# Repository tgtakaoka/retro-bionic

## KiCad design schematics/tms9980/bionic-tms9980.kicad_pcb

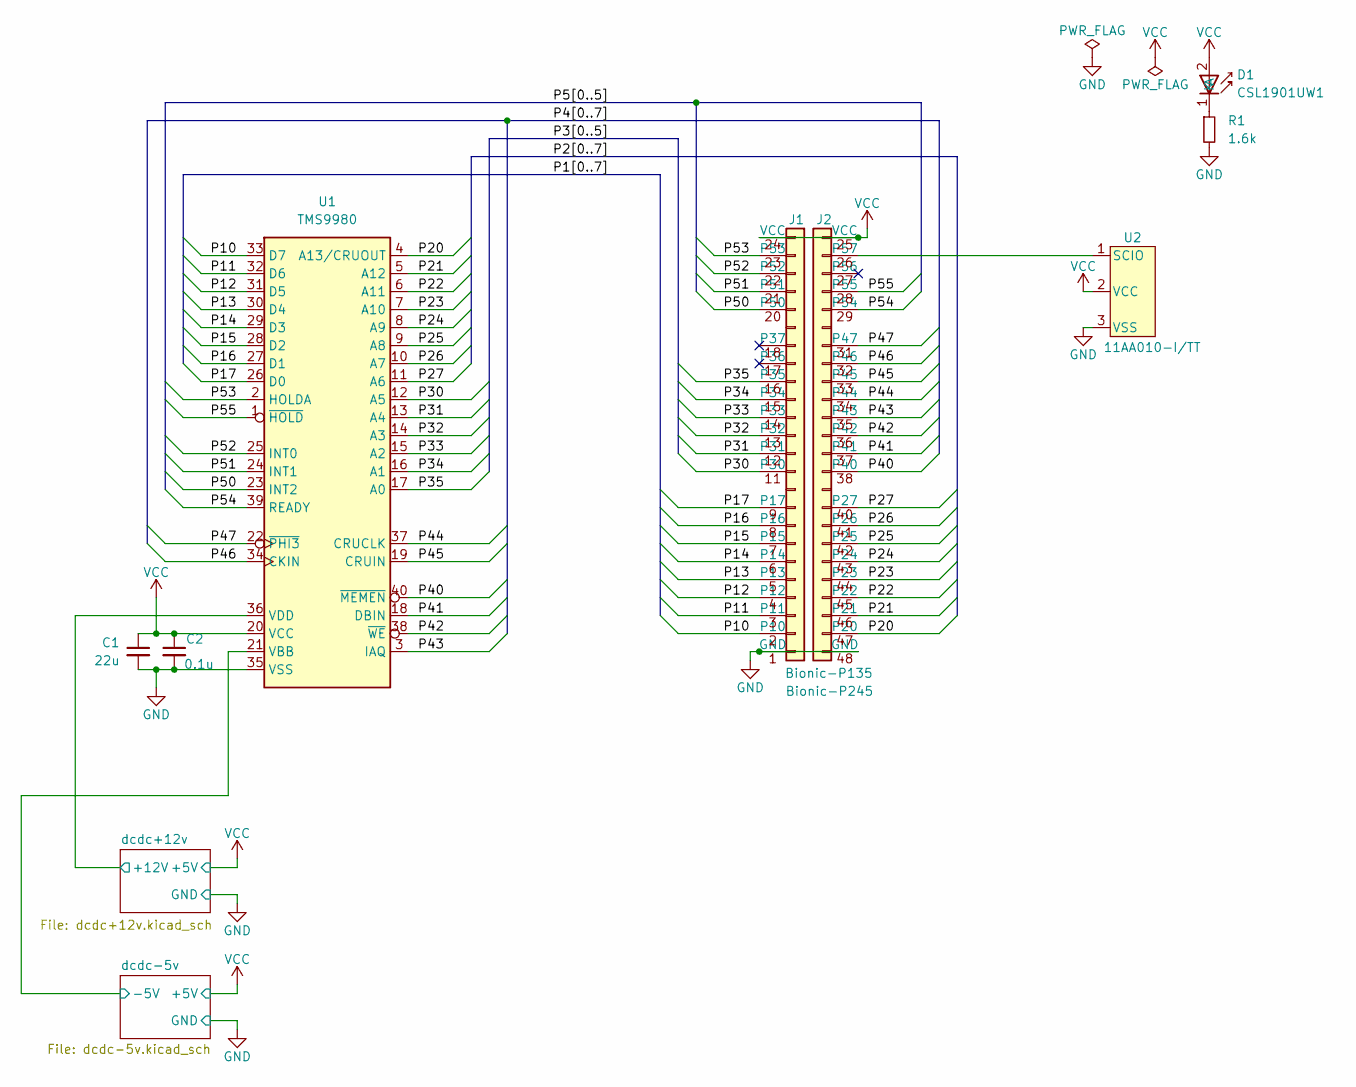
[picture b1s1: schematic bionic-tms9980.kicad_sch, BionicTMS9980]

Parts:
C1: 22u; C_0603_1608Metric_Pad1.08x0.95mm_HandSolder
C2: 0.1u; C_0603_1608Metric_Pad1.08x0.95mm_HandSolder
D1: CSL1901UW1; LED_CSL1901UW1_ROM-M
J1: Bionic-P135; Bionic-P135_THT
J2: Bionic-P245; Bionic-P245_THT
R1: 1.6k; R_0603_1608Metric_Pad0.98x0.95mm_HandSolder
U1: TMS9980; DIP-40_W15.24mm_Socket
U2: 11AA010-I/TT; SOT-23_MC_MCH-M

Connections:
/P10: J1.2 (P10), U1.33 (D7)
/P11: J1.3 (P11), U1.32 (D6)
/P12: J1.4 (P12), U1.31 (D5)
/P13: J1.5 (P13), U1.30 (D4)
/P14: J1.6 (P14), U1.29 (D3)
/P15: J1.7 (P15), U1.28 (D2)
/P16: J1.8 (P16), U1.27 (D1)
/P17: J1.9 (P17), U1.26 (D0)
/P20: J2.47 (P20), U1.4 (A13/CRUOUT)
/P21: J2.46 (P21), U1.5 (A12)
/P22: J2.45 (P22), U1.6 (A11)
/P23: J2.44 (P23), U1.7 (A10)
/P24: J2.43 (P24), U1.8 (A9)
/P25: J2.42 (P25), U1.9 (A8)
/P26: J2.41 (P26), U1.10 (A7)
/P27: J2.40 (P27), U1.11 (A6)
/P30: J1.11 (P30), U1.12 (A5)
/P31: J1.12 (P31), U1.13 (A4)
/P32: J1.13 (P32), U1.14 (A3)
/P33: J1.14 (P33), U1.15 (A2)
/P34: J1.15 (P34), U1.16 (A1)
/P35: J1.16 (P35), U1.17 (A0)
/P40: J2.38 (P40), U1.40 (~MEMEN)
/P41: J2.37 (P41), U1.18 (DBIN)
/P42: J2.36 (P42), U1.38 (~WE)
/P43: J2.35 (P43), U1.3 (IAQ)
/P44: J2.34 (P44), U1.37 (CRUCLK)
/P45: J2.33 (P45), U1.19 (CRUIN)
/P46: J2.32 (P46), U1.34 (CKIN)
/P47: J2.31 (P47), U1.22 (~PHI3)
/P50: J1.20 (P50), U1.23 (INT2)
/P51: J1.21 (P51), U1.24 (INT1)
/P52: J1.22 (P52), U1.25 (INT0)
/P53: J1.23 (P53), U1.2 (HOLDA)
/P54: J2.29 (P54), U1.39 (READY)
/P55: J2.28 (P55), U1.1 (~HOLD)
/dcdc+12v/+12V: U1.36 (VDD); also elsewhere on the board
/dcdc-5v/-5V: U1.21 (VBB); also elsewhere on the board
GND: C1.2, C2.2, J1.1 (GND), J2.48 (GND), R1.2, U1.35 (VSS), U2.3 (VSS); also elsewhere on the board
unnamed: D1.1 (K), R1.1
unnamed: J2.26 (P57), U2.1 (SCIO)
VCC: C1.1, C2.1, D1.2 (A), J1.24 (VCC), J2.25 (VCC), U1.20 (VCC), U2.2 (VCC); also elsewhere on the board

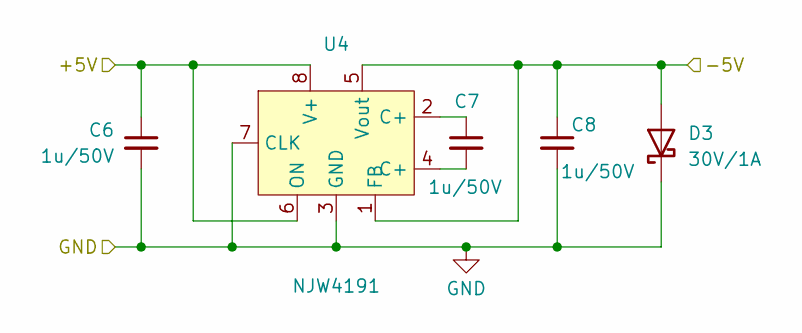
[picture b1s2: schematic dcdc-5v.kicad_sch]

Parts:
C6, C7, C8: 1u/50V; C_0603_1608Metric_Pad1.08x0.95mm_HandSolder
D3: 30V/1A; CR_60M-60_ROM-M
U4: NJW4191; MSOP8VSP8_PI-VSP8-E-B_NMD-M

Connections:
/dcdc-5v/-5V: C8.1, D3.2 (A), U4.1 (FB), U4.5 (Vout); also elsewhere on the board
GND: C6.2, C8.2, D3.1 (K), U4.3 (GND), U4.7 (CLK); also elsewhere on the board
unnamed: C7.1, U4.2 (C+)
unnamed: C7.2, U4.4 (C+)
VCC: C6.1, U4.6 (ON), U4.8 (V+); also elsewhere on the board

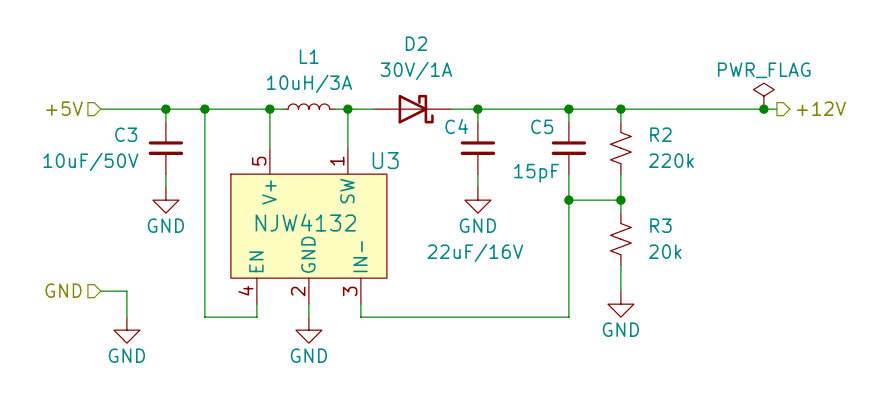
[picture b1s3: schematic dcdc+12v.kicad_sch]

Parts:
C3: 10uF/50V; C_0603_1608Metric_Pad1.08x0.95mm_HandSolder
C4: 22uF/16V; C_0603_1608Metric_Pad1.08x0.95mm_HandSolder
C5: 15pF; C_0603_1608Metric_Pad1.08x0.95mm_HandSolder
D2: 30V/1A; CR_60M-60_ROM-M
L1: 10uH/3A; IND_DFE322512F_MUR-M
R2: 220k; R_0603_1608Metric_Pad0.98x0.95mm_HandSolder
R3: 20k; R_0603_1608Metric_Pad0.98x0.95mm_HandSolder
U3: NJW4132; SOT-89-5_NMD-M

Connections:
/dcdc+12v/+12V: C4.1, C5.1, D2.1 (K), R2.1; also elsewhere on the board
GND: C3.2, C4.2, R3.2, U3.2 (GND); also elsewhere on the board
unnamed: D2.2 (A), L1.2, U3.1 (SW)
unnamed: C5.2, R2.2, R3.1, U3.3 (IN-)
VCC: C3.1, L1.1, U3.4 (EN), U3.5 (V+); also elsewhere on the board

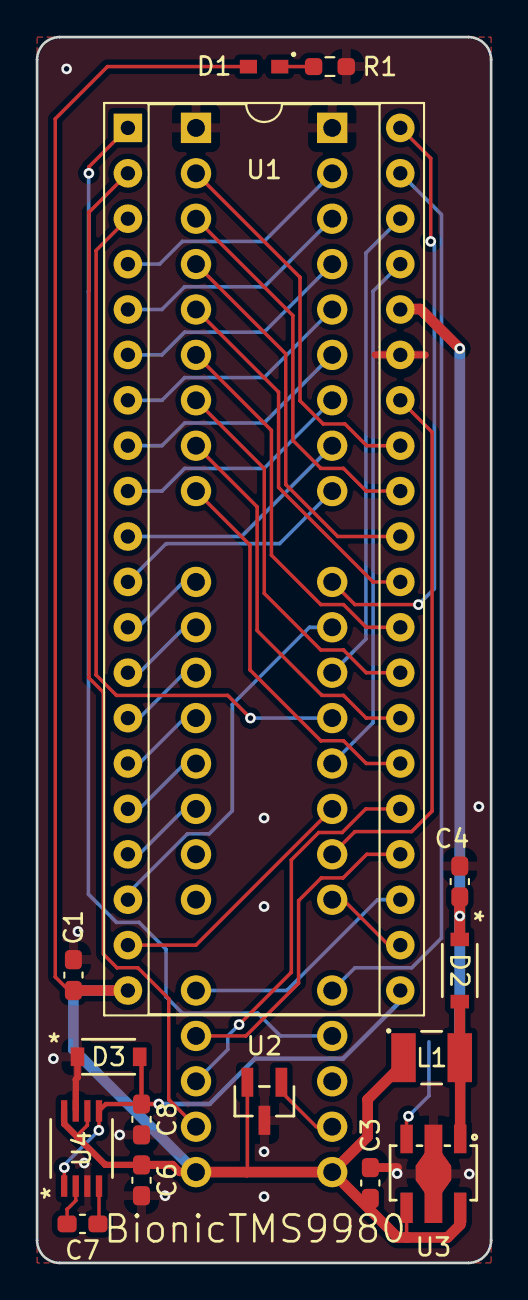
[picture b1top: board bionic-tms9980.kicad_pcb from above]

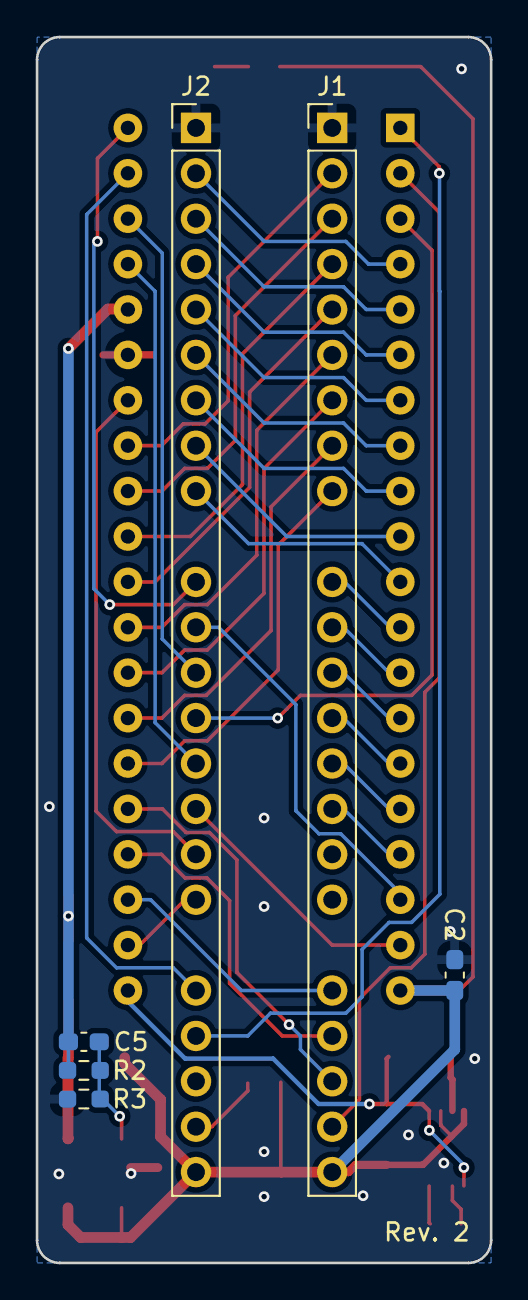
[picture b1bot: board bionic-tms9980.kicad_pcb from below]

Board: 2 copper layers, 25.4 x 68.6 mm, 21 parts (6 on the bottom side), 46 nets.

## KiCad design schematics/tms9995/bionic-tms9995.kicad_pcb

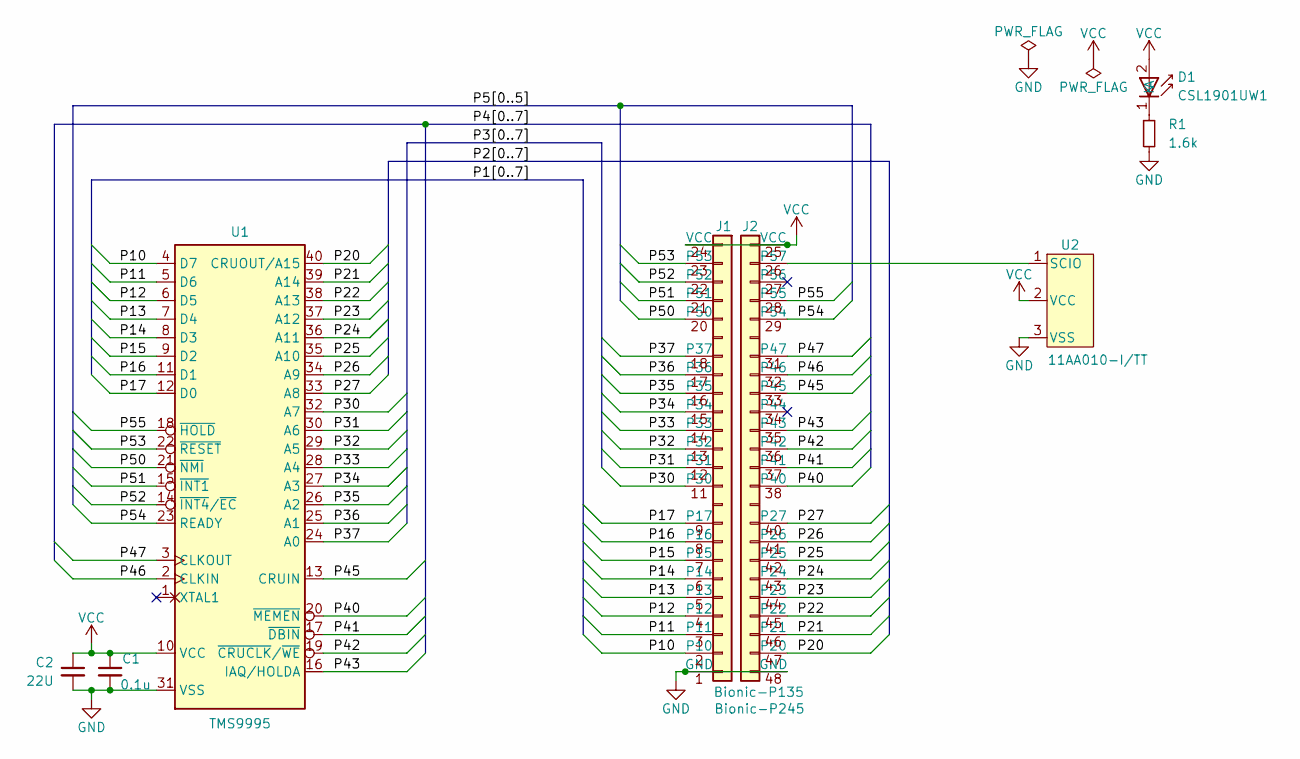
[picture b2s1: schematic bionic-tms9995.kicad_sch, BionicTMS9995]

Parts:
C1: 0.1u; C_0603_1608Metric_Pad1.08x0.95mm_HandSolder
C2: 22U; C_0603_1608Metric_Pad1.08x0.95mm_HandSolder
D1: CSL1901UW1; LED_CSL1901UW1_ROM-M
J1: Bionic-P135; Bionic-P135_THT
J2: Bionic-P245; Bionic-P245_THT
R1: 1.6k; R_0603_1608Metric_Pad0.98x0.95mm_HandSolder
U1: TMS9995; DIP-40_W15.24mm_Socket
U2: 11AA010-I/TT; SOT-23_MC_MCH-M

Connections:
/P10: J1.2 (P10), U1.4 (D7)
/P11: J1.3 (P11), U1.5 (D6)
/P12: J1.4 (P12), U1.6 (D5)
/P13: J1.5 (P13), U1.7 (D4)
/P14: J1.6 (P14), U1.8 (D3)
/P15: J1.7 (P15), U1.9 (D2)
/P16: J1.8 (P16), U1.11 (D1)
/P17: J1.9 (P17), U1.12 (D0)
/P20: J2.47 (P20), U1.40 (CRUOUT/A15)
/P21: J2.46 (P21), U1.39 (A14)
/P22: J2.45 (P22), U1.38 (A13)
/P23: J2.44 (P23), U1.37 (A12)
/P24: J2.43 (P24), U1.36 (A11)
/P25: J2.42 (P25), U1.35 (A10)
/P26: J2.41 (P26), U1.34 (A9)
/P27: J2.40 (P27), U1.33 (A8)
/P30: J1.11 (P30), U1.32 (A7)
/P31: J1.12 (P31), U1.30 (A6)
/P32: J1.13 (P32), U1.29 (A5)
/P33: J1.14 (P33), U1.28 (A4)
/P34: J1.15 (P34), U1.27 (A3)
/P35: J1.16 (P35), U1.26 (A2)
/P36: J1.17 (P36), U1.25 (A1)
/P37: J1.18 (P37), U1.24 (A0)
/P40: J2.38 (P40), U1.20 (~MEMEN)
/P41: J2.37 (P41), U1.17 (~DBIN)
/P42: J2.36 (P42), U1.19 (~CRUCLK/~WE)
/P43: J2.35 (P43), U1.16 (IAQ/HOLDA)
/P45: J2.33 (P45), U1.13 (CRUIN)
/P46: J2.32 (P46), U1.2 (CLKIN)
/P47: J2.31 (P47), U1.3 (CLKOUT)
/P50: J1.20 (P50), U1.21 (~NMI)
/P51: J1.21 (P51), U1.15 (~INT1)
/P52: J1.22 (P52), U1.14 (~INT4/~EC)
/P53: J1.23 (P53), U1.22 (~RESET)
/P54: J2.29 (P54), U1.23 (READY)
/P55: J2.28 (P55), U1.18 (~HOLD)
GND: C1.2, C2.2, J1.1 (GND), J2.48 (GND), R1.2, U1.31 (VSS), U2.3 (VSS)
unnamed: D1.1 (K), R1.1
unnamed: J2.26 (P57), U2.1 (SCIO)
VCC: C1.1, C2.1, D1.2 (A), J1.24 (VCC), J2.25 (VCC), U1.10 (VCC), U2.2 (VCC)

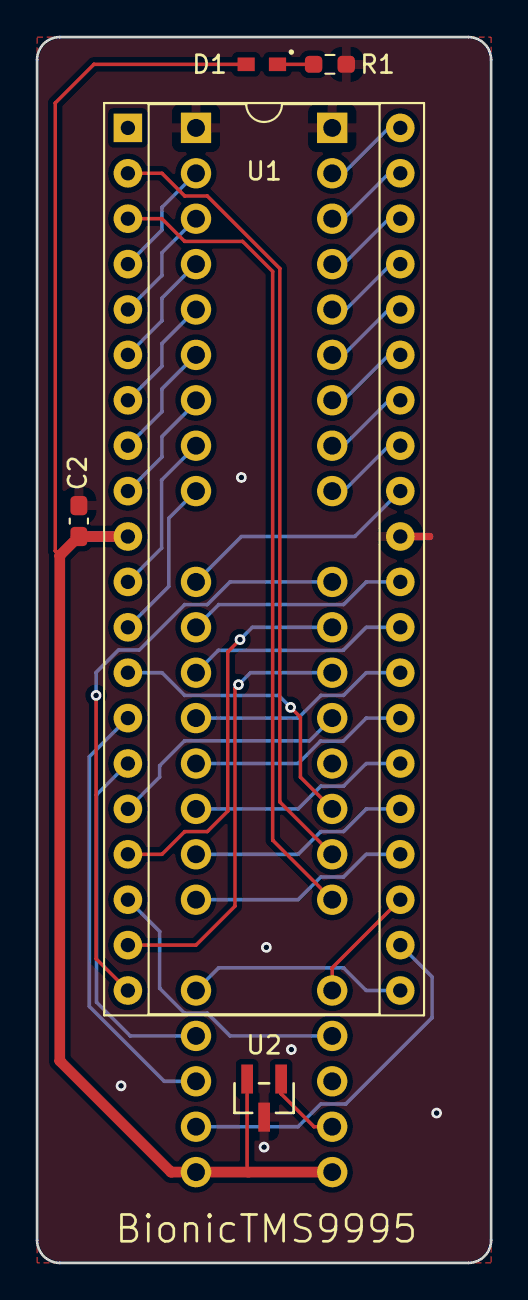
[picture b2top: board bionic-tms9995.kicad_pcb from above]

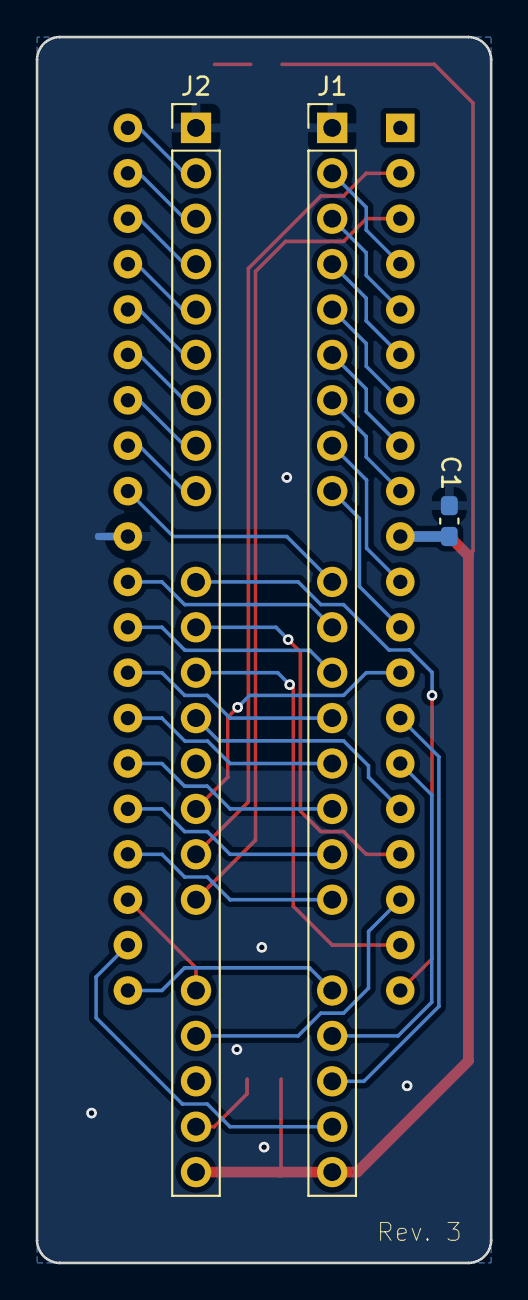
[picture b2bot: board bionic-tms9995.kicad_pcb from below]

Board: 2 copper layers, 25.4 x 68.6 mm, 8 parts (3 on the bottom side), 41 nets.

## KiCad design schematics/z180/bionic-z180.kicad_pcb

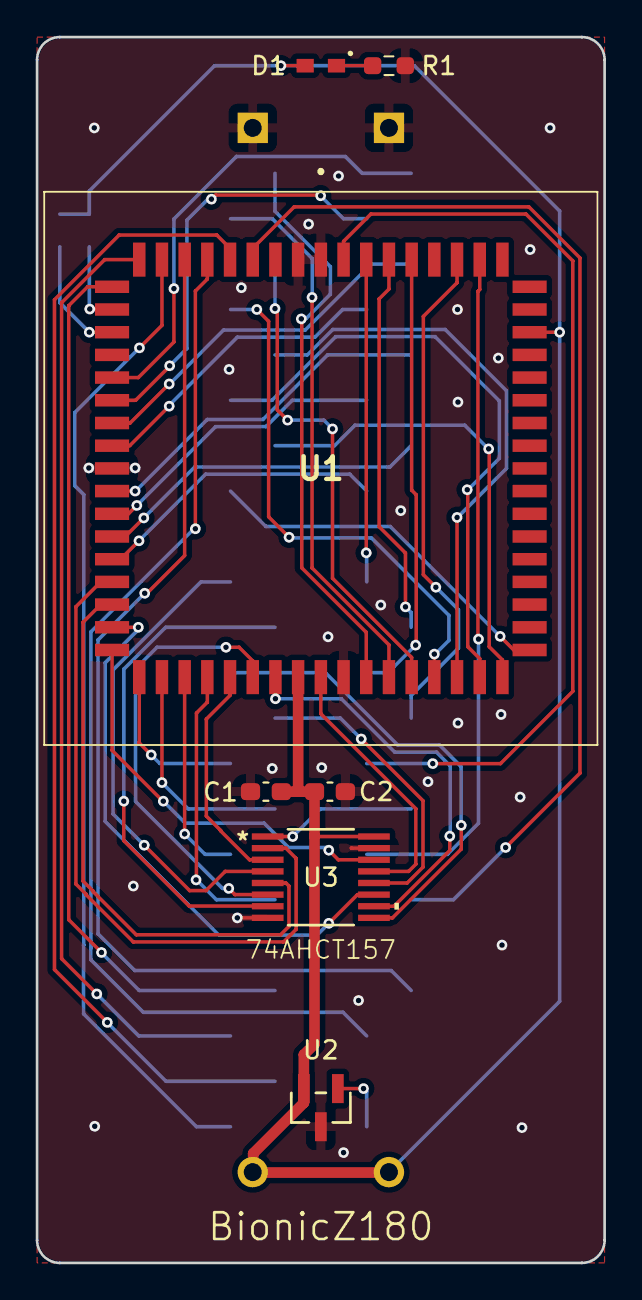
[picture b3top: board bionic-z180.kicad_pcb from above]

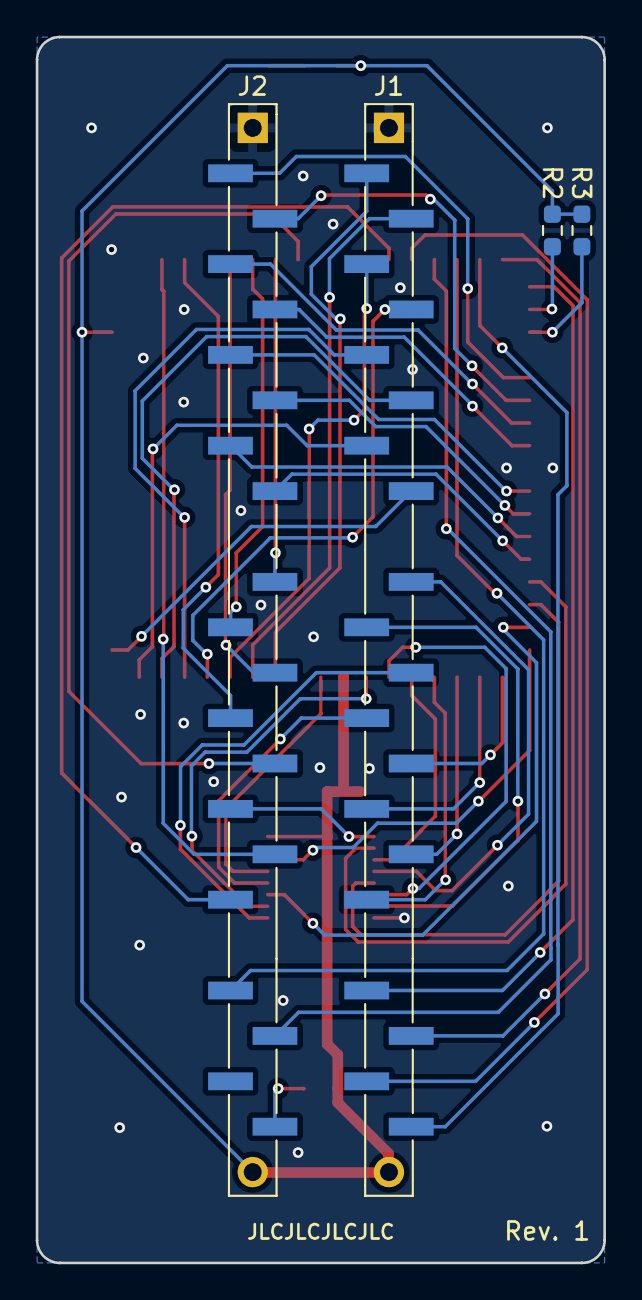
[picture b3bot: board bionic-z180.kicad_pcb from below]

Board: 2 copper layers, 31.7 x 68.6 mm, 11 parts (4 on the bottom side), 52 nets.

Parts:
C1: 0.1u; C_0603_1608Metric_Pad1.08x0.95mm_HandSolder
C2: 22u; C_0603_1608Metric_Pad1.08x0.95mm_HandSolder
D1: CSL1901UW1; LED_CSL1901UW1_ROM-M
J1: Bionic-P135; Bionic-P135_SMT
J2: Bionic-P245; Bionic-P245_SMT
R1: 1.6k; R_0603_1608Metric_Pad0.98x0.95mm_HandSolder
R2, R3: 10k; R_0603_1608Metric_Pad0.98x0.95mm_HandSolder
U1: Z80180; 846821B1RKTP
U2: 11AA010-I/TT; SOT-23_MC_MCH-M
U3: 74AHCT157; PW16-M

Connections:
A0: J2.47 (P20), U1.14 (A0)
A1: J2.46 (P21), U1.15 (A1)
A2: J2.45 (P22), U1.16 (A2)
A3: J2.44 (P23), U1.17 (A3)
A4: J2.43 (P24), U1.19 (A4)
A5: J2.42 (P25), U1.20 (A5)
A6: J2.41 (P26), U1.21 (A6)
A7: J2.40 (P27), U1.22 (A7)
A8: U1.23 (A8), U3.2 (1I0)
A9: U1.24 (A9), U3.5 (2I0)
A10: U1.25 (A10), U3.11 (3I0)
A11: U1.26 (A11), U3.14 (4I0)
A12: J1.15 (P34), U1.27 (A12)
A13: J1.16 (P35), U1.28 (A13)
A14: J1.17 (P36), U1.29 (A14)
A15: J1.18 (P37), U1.30 (A15)
A16: U1.31 (A16), U3.3 (1I1)
A17: U1.32 (A17), U3.6 (2I1)
A18: U1.33 (A18), U3.10 (3I1)
A19: U1.35 (A19), U3.13 (4I1)
ASEL: J2.33 (P45), U3.1 (S)
D0: J1.2 (P10), U1.37 (D0)
D1: J1.3 (P11), U1.38 (D1)
D2: J1.4 (P12), U1.39 (D2)
D3: J1.5 (P13), U1.40 (D3)
D4: J1.6 (P14), U1.41 (D4)
D5: J1.7 (P15), U1.42 (D5)
D6: J1.8 (P16), U1.43 (D6)
D7: J1.9 (P17), U1.44 (D7)
EXTAL: J2.31 (P47), U1.4 (EXTAL)
GND: C1.2, C2.2, J1.1 (GND), J2.48 (GND), R1.2, U1.1 (V_{SS}), U1.2 (V_{SS}), U1.18 (V_{SS}), U1.36 (V_{SS}), U2.3 (VSS), U3.8 (GND), U3.15 (~E)
unnamed: D1.1 (K), R1.1
unnamed: J2.26 (P57), U2.1 (SCIO)
unnamed: R2.2, U1.11 (~INT1)
unnamed: R3.2, U1.12 (~INT2)
P30: J1.11 (P30), U3.4 (1Y)
P31: J1.12 (P31), U3.7 (2Y)
P32: J1.13 (P32), U3.9 (3Y)
P33: J1.14 (P33), U3.12 (4Y)
PHI: J2.34 (P44), U1.68 (PHI)
VCC: C1.1, C2.1, D1.2 (A), J1.24 (VCC), J2.25 (VCC), R2.1, R3.1, U1.34 (V_{CC}), U1.58 (~DREQ1), U2.2 (VCC), U3.16 (Vcc)
~BUSACK: J2.28 (P55), U1.6 (~BUSACK)
~BUSREQ: J2.29 (P54), U1.7 (~BUSREQ)
~INT0: J1.20 (P50), U1.10 (~INT0)
~IORQ: J2.32 (P46), U1.62 (~IORQ)
~M1: J2.36 (P42), U1.65 (~M1)
~MREQ: J2.35 (P43), U1.63 (~MREQ)
~NMI: J1.21 (P51), U1.9 (~NMI)
~RD: J2.38 (P40), U1.67 (~RD)
~RESET: J1.23 (P53), U1.8 (~RESET)
~WAIT: J1.22 (P52), U1.5 (~WAIT)
~WR: J2.37 (P41), U1.66 (~WR)
